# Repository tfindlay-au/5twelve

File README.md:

# 5 Twelve

This project is a simple power adaptor - it draws 5v from the USB micro B port and provides 12v via the 10-pin header.

### Design

This board uses the minimum components and tried to standardise on 0603 packages

|Part number        |Description        |
|-------------------|-------------------|
|PAM2423            |DC-DC Converter    |
|SDFL1608S6R8MTF    |Sunlord Inductor   |
|TSW-105-23-F-D-010 |2x5 pin header     |
|USB3140-30-0230-1-C|USB Micro B port   |
|SS34-E3/9AT        |Circuit protection |
|VLMW1300-GS08      |LED indicator      |

### Safety
The design uses a simple Shottky diode to protect the DC-DC converter

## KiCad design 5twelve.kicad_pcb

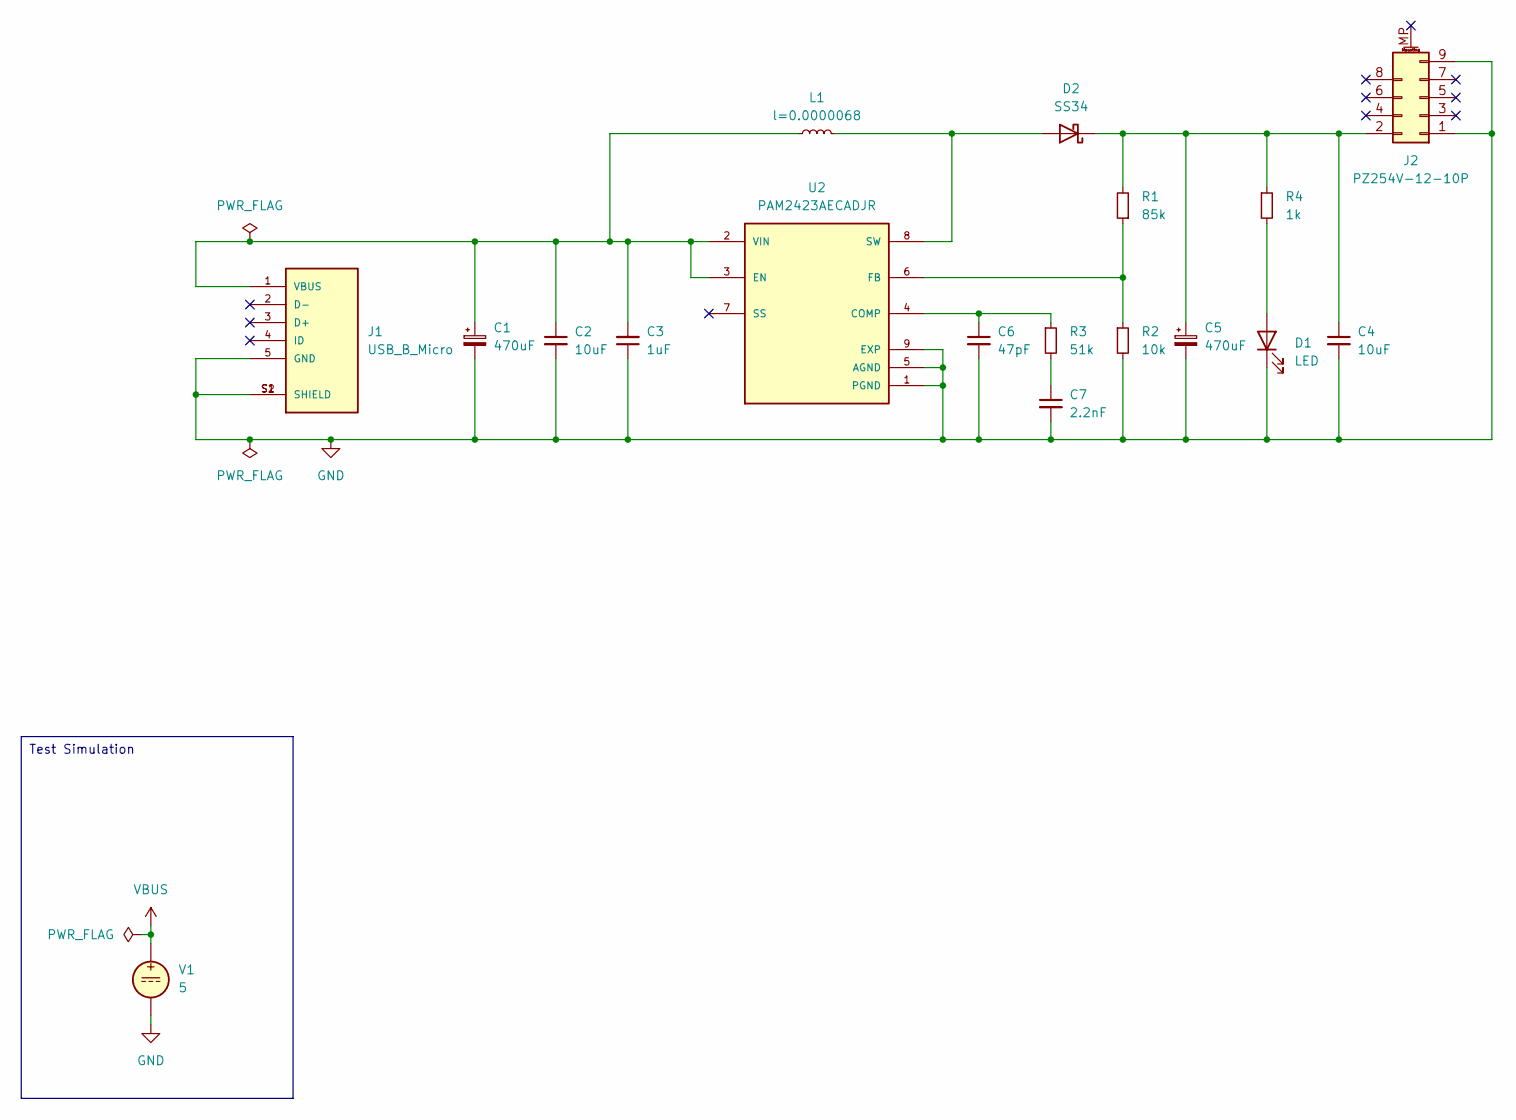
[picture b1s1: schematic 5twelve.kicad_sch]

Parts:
C1, C5: 470uF; C_Elec_8x10.2; LCSC C161936
C2, C4: 10uF; C_0603_1608Metric; LCSC C596327
C3: 1uF; C_0603_1608Metric; LCSC C14664
C6: 47pF; C_0603_1608Metric; LCSC C519392
C7: 2.2nF; C_0603_1608Metric; LCSC C309471
D1: LED; LED_0603_1608Metric; LCSC C413463
D2: SS34; D_SMC
J1: USB_B_Micro; GCT_USB3140-30-0230-1-C_REVE1; LCSC C6007483
J2: PZ254V-12-10P; PinHeader_2x05_P2.54mm_Vertical; LCSC C492422
L1: l=0.0000068; L_0603_1608Metric; LCSC C279872
R1: 85k; R_0603_1608Metric
R2: 10k; R_0603_1608Metric
R3: 51k; R_0603_1608Metric
R4: 1k; R_0603_1608Metric
U2: PAM2423AECADJR; SOIC127P600X163-9N
V1: 5

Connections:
GND: C1.2, C2.2, C3.1, C4.2, C5.2, C6.2, C7.2, D1.1 (K), J1.5 (GND), J1.S1 (SHIELD), J1.S2 (SHIELD), J2.1, J2.9, R2.2, U2.1 (PGND), U2.5 (AGND), U2.9 (EXP), V1.2
unnamed: C7.1, R3.2
unnamed: D1.2 (A), R4.2
unnamed: D2.2 (A), L1.2, U2.8 (SW)
unnamed: C4.1, C5.1, D2.1 (K), J2.2, R1.2, R4.1
unnamed: C1.1, C2.1, C3.2, J1.1 (VBUS), L1.1, U2.2 (VIN), U2.3 (EN)
unnamed: C6.1, R3.1, U2.4 (COMP)
unnamed: R1.1, R2.1, U2.6 (FB)

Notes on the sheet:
Test Simulation

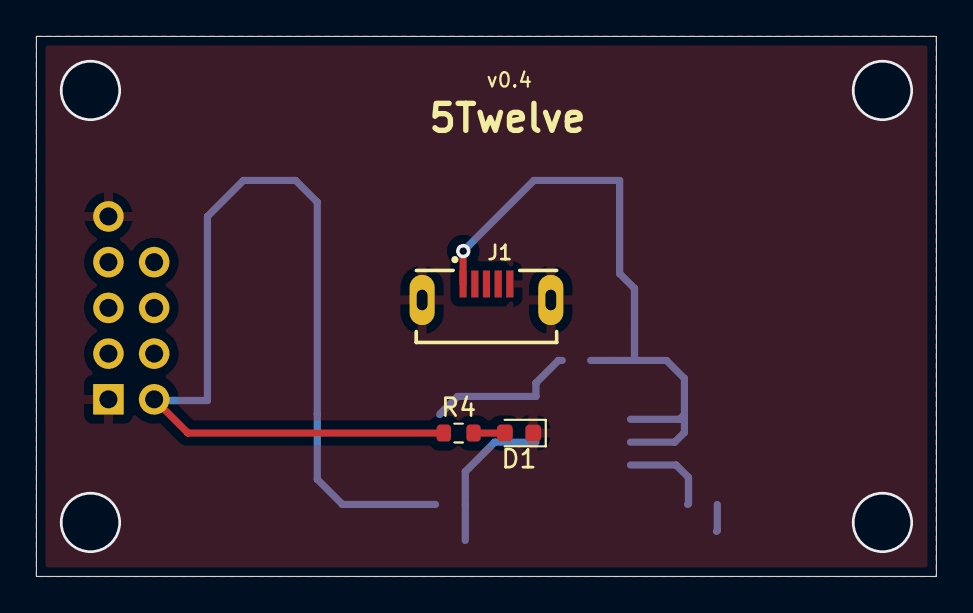
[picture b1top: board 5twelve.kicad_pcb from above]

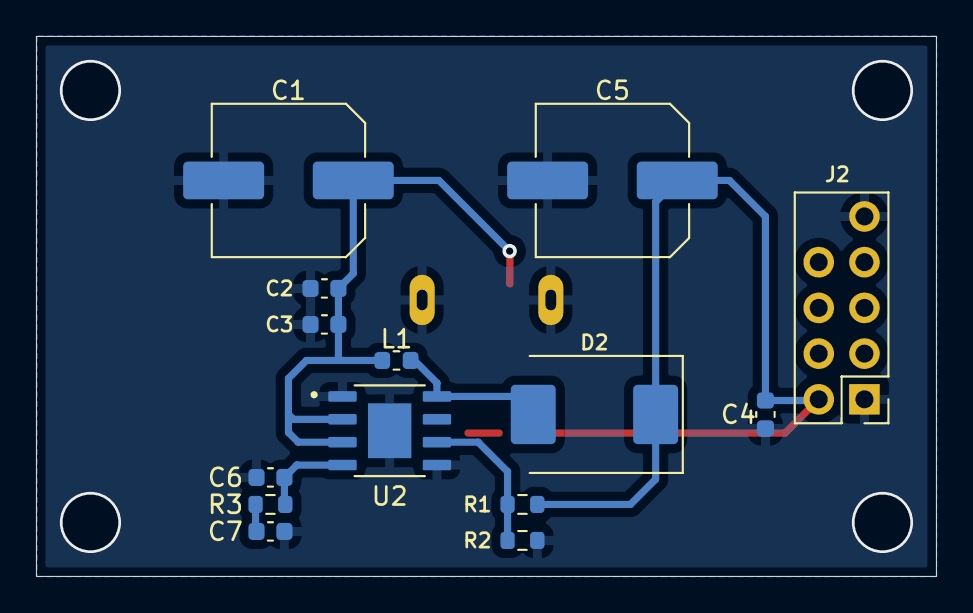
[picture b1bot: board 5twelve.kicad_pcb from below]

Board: 2 copper layers, 50.0 x 30.0 mm, 17 parts (14 on the bottom side), 8 nets.

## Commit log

2024-12-20 Setup
2024-12-20 Project upload
2024-12-20 Correction
